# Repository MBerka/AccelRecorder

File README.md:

This project contains PCB and firmware files for the AccelRecorder wearable, capable of recording tri-axial accelerations or, with firmware adjustments, communicating with a combined accelerometer/gyroscope chip. The byte-encoded output of the firmware can be parsed and interpreted with the PC-side software of the AccelPanel repository.

The Eagle files in /PCB that can be etched chemically via toner transfer, or exported for commercial PCB manufacturing.

The C project was written and compiled through Atmel Studio 7. Compiled binaries are available in /Hardware/Debug.

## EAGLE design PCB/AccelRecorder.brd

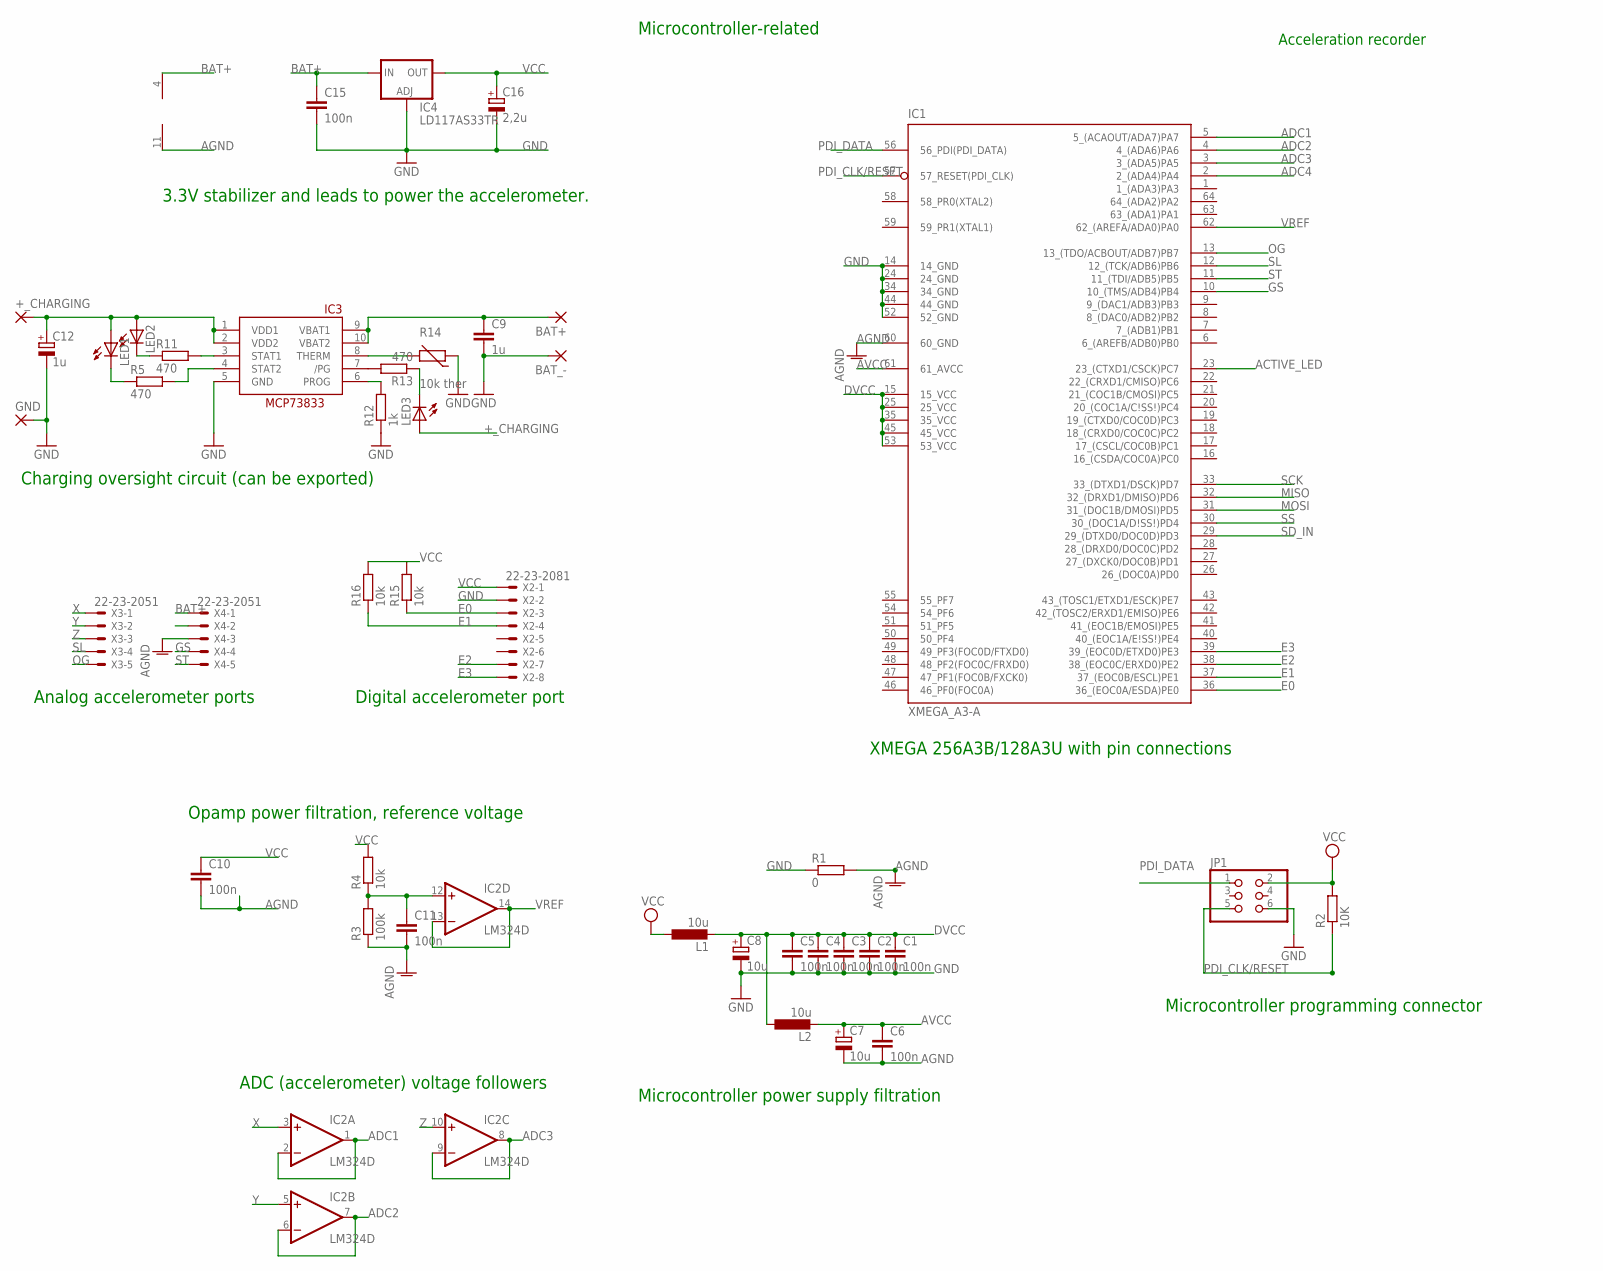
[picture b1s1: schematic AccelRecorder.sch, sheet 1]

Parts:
+_CHARGING: SMD2; SMD1,27-2,54
BAT+: SMD2; SMD1,27-2,54
BAT_-: SMD2; SMD1,27-2,54
C1, C2, C3, C4, C5, C6, C15: 100n; C0805K
C7, C8: 10u; SANYO-OSCON_SMD_B6
C9: 1u; C1206
C10, C11: 100n; C0805
C12: 1u; SANYO-OSCON_SMD_B6
C16: 2,2u; SANYO-OSCON_SMD_B6
GND: SMD2; SMD1,27-2,54
IC1: XMEGA_A3-A; TQFP64
IC2: LM324D; SO14
IC3: MCP73833-UN; MSOP10
IC4: LD117AS33TR; SOT223
JP1: PINHD-2X3; 2X03
L1, L2: 10u; L3225M
LED1, LED2, LED3: LED3MM
R1: 0; M1206
R2: 10K; M1206
R3: 100k; M1206
R4, R15, R16: 10k; M1206
R5, R11, R13: 470; R0805
R12: 1k; R0805
R14: 10k ther; RS-2,5
X2: 22-23-2081
X3, X4: 22-23-2051

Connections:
+_CHARGING: +_CHARGING.1, C12.+, IC3.1 (VDD1), IC3.2 (VDD2), LED1.A, LED2.A, LED3.A
ACTIVE_LED: IC1.23 (23_(CTXD1/CSCK)PC7); also elsewhere on the board
ADC1: IC1.5 (5_(ACAOUT/ADA7)PA7), IC2.1 (OUT), IC2.2 (-IN)
ADC2: IC1.4 (4_(ADA6)PA6), IC2.6 (-IN), IC2.7 (OUT)
ADC3: IC1.3 (3_(ADA5)PA5), IC2.8 (OUT), IC2.9 (-IN)
ADC4: IC1.2 (2_(ADA4)PA4)
AGND: C6.2, C7.-, C10.2, C11.2, IC1.60 (60_GND), IC2.11 (V-), R1.2, R3.1, X4.3
AVCC: C6.1, C7.+, IC1.61 (61_AVCC), L2.2
BAT+: BAT+.1, C9.1, C15.1, IC2.4 (V+), IC3.9 (VBAT1), IC3.10 (VBAT2), IC4.3 (IN), X4.1
DVCC: C1.1, C2.1, C3.1, C4.1, C5.1, C8.+, IC1.15 (15_VCC), IC1.25 (25_VCC), IC1.35 (35_VCC), IC1.45 (45_VCC), IC1.53 (53_VCC), L1.2, L2.1
E0: IC1.36 (36_(EOC0A/ESDA)PE0), R15.1, X2.3
E1: IC1.37 (37_(EOC0B/ESCL)PE1), R16.1, X2.4
E2: IC1.38 (38_(EOC0C/ERXD0)PE2), X2.7
E3: IC1.39 (39_(EOC0D/ETXD0)PE3), X2.8
GND: BAT_-.1, C1.2, C2.2, C3.2, C4.2, C5.2, C8.-, C9.2, C12.-, C15.2, C16.-, GND.1, IC1.14 (14_GND), IC1.24 (24_GND), IC1.34 (34_GND), IC1.44 (44_GND), IC1.52 (52_GND), IC3.5 (GND), IC4.1 (ADJ), JP1.6, R1.1, R12.1, R14.1, X2.2; also elsewhere on the board
GS: IC1.10 (10_(TMS/ADB4)PB4), X4.4
MISO: IC1.32 (32_(DRXD1/DMISO)PD6); also elsewhere on the board
MOSI: IC1.31 (31_(DOC1B/DMOSI)PD5); also elsewhere on the board
unnamed: IC3.7 (/PG), R13.2
unnamed: LED3.K (C), R13.1
unnamed: IC3.3 (STAT1), R11.2
unnamed: LED2.K (C), R11.1
unnamed: C11.1, IC2.12 (+IN), R3.2, R4.1
unnamed: IC3.6 (PROG), R12.2
unnamed: IC3.8 (THERM), R14.2
unnamed: LED1.K (C), R5.1
unnamed: IC3.4 (STAT2), R5.2
OG: IC1.13 (13_(TDO/ACBOUT/ADB7)PB7), X3.5
PDI_CLK/RESET: IC1.57 (57_RESET(PDI_CLK)), JP1.5, R2.1
PDI_DATA: IC1.56 (56_PDI(PDI_DATA)), JP1.1
SCK: IC1.33 (33_(DTXD1/DSCK)PD7); also elsewhere on the board
SD_IN: IC1.29 (29_(DTXD0/DOC0D)PD3); also elsewhere on the board
SL: IC1.12 (12_(TCK/ADB6)PB6), X3.4
SS: IC1.30 (30_(DOC1A/D\!SS\!)PD4); also elsewhere on the board
ST: IC1.11 (11_(TDI/ADB5)PB5), X4.5
VCC: C10.1, C16.+, IC4.4 (OUT), JP1.2, L1.1, R2.2, R4.2, R15.2, R16.2, X2.1; also elsewhere on the board
VREF: IC1.62 (62_(AREFA/ADA0)PA0), IC2.13 (-IN), IC2.14 (OUT)
X: IC2.3 (+IN), X3.1
Y: IC2.5 (+IN), X3.2
Z: IC2.10 (+IN), X3.3

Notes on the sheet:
Microcontroller-related
Microcontroller programming connector
Microcontroller power supply filtration
XMEGA 256A3B/128A3U with pin connections
Acceleration recorder
Opamp power filtration, reference voltage
ADC (accelerometer) voltage followers
Charging oversight circuit (can be exported)
3.3V stabilizer and leads to power the accelerometer.
Analog accelerometer ports
Digital accelerometer port

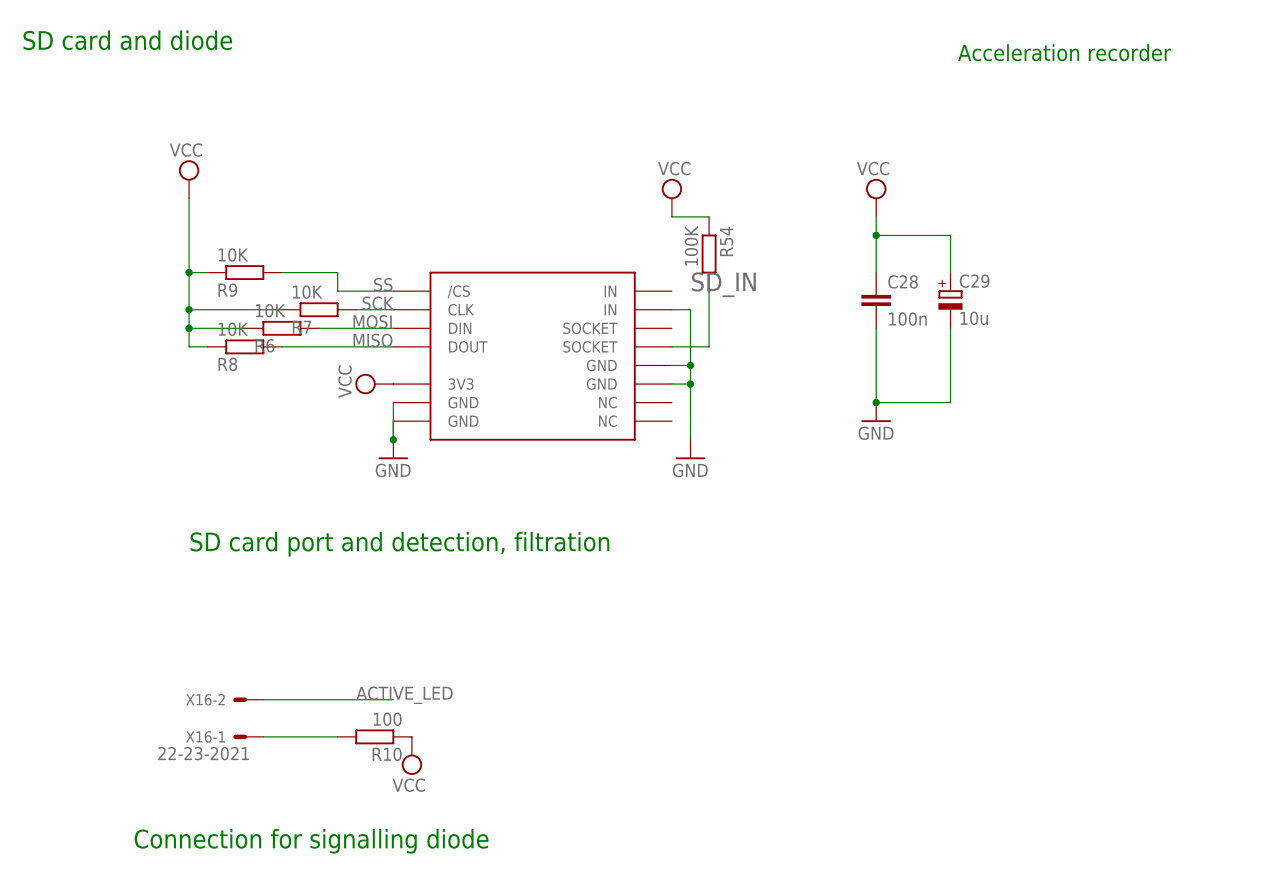
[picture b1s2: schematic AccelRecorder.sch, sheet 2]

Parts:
C28: 100n; C0805K
C29: 10u; SANYO-OSCON_SMD_B6
R6, R7, R8, R9: 10K; M1206
R10: 100; M1206
R54: 100K; M1206
U$1: MMC; MMC_SOCKET
X16: 22-23-2021; MPN 22-23-2021

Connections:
ACTIVE_LED: X16.2; also elsewhere on the board
GND: C28.2, C29.-, U$1.GND@1 (GND), U$1.GND@2 (GND), U$1.GND@3 (GND), U$1.GND@4 (GND), U$1.IN@2 (IN); also elsewhere on the board
MISO: R8.2, U$1.DOUT; also elsewhere on the board
MOSI: R6.2, U$1.DIN; also elsewhere on the board
unnamed: R10.2, X16.1
SCK: R7.2, U$1.CLK; also elsewhere on the board
SD_IN: R54.2, U$1.P$2 (SOCKET); also elsewhere on the board
SS: R9.2, U$1./CS; also elsewhere on the board
VCC: C28.1, C29.+, R6.1, R7.1, R8.1, R9.1, R10.1, R54.1, U$1.3V3; also elsewhere on the board

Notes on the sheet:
SD card and diode
SD card port and detection, filtration
Acceleration recorder
Connection for signalling diode

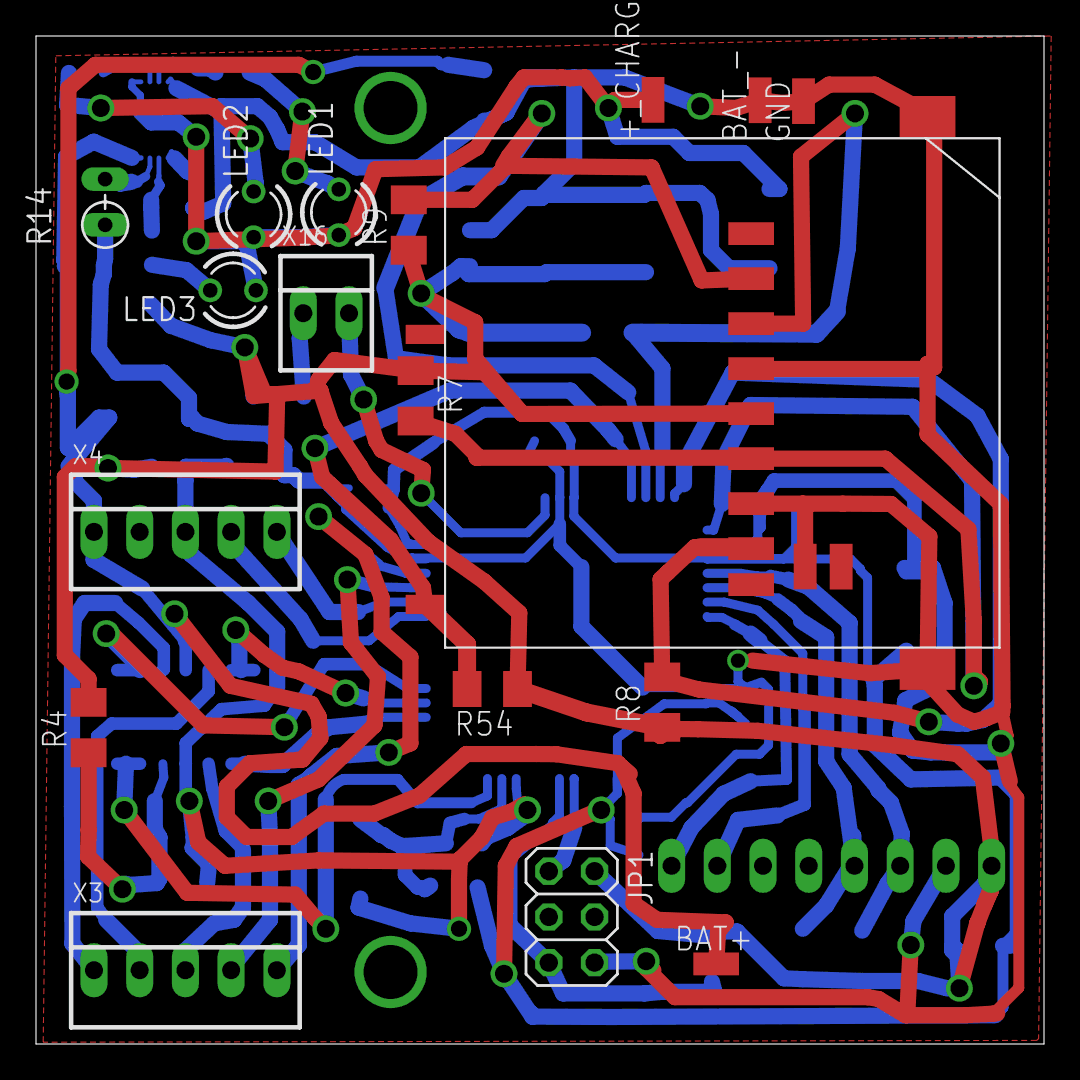
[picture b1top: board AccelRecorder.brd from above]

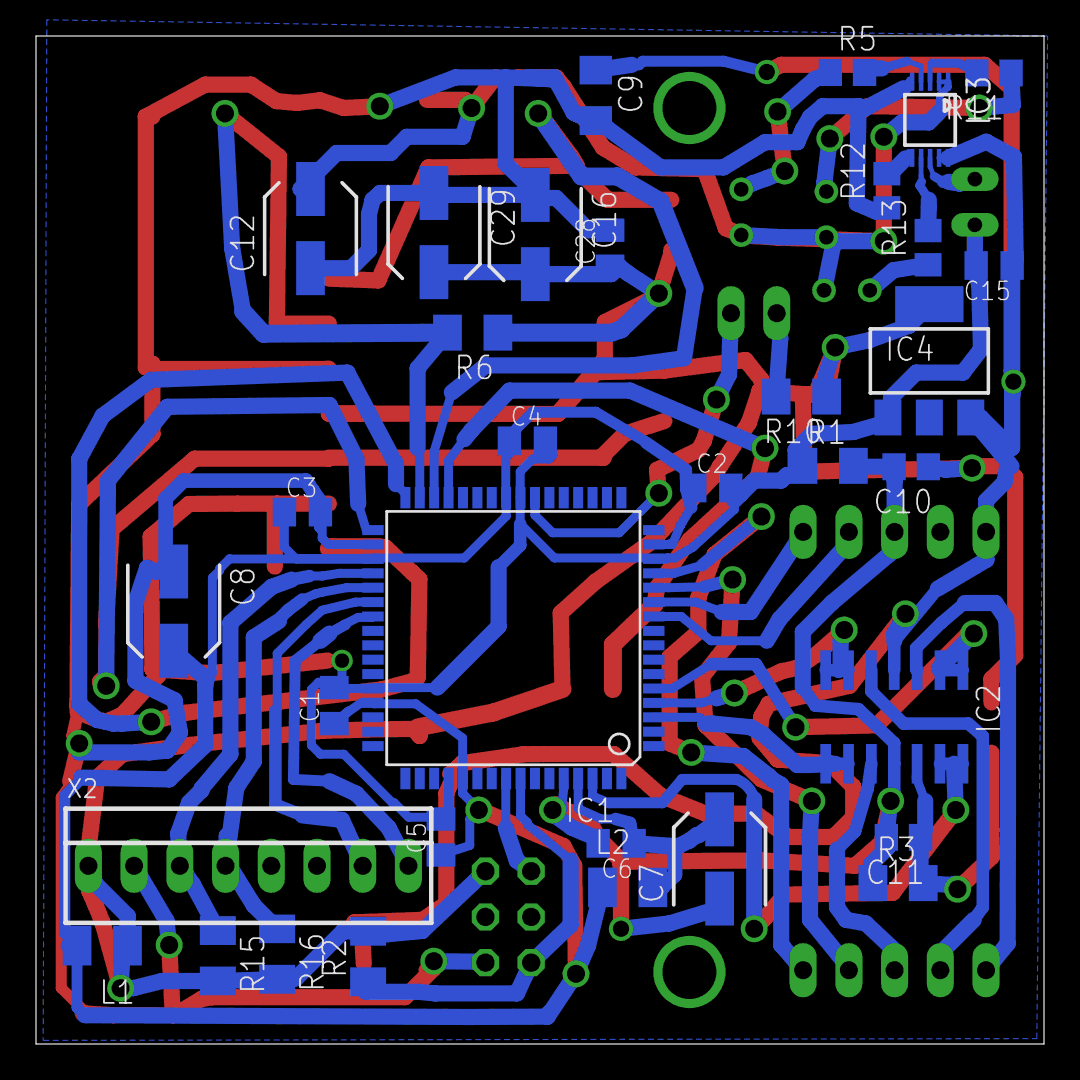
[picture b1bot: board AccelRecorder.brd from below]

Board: 2 copper layers, 56.0 x 56.0 mm, 52 parts (34 on the bottom side), 40 nets.

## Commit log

2018-07-14 Dual-accelerometer version detailed in thesis.
